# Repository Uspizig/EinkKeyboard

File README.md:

# EinkKeyboard

Please see full details here:
https://hackaday.io/project/185789-lowpow-e-ink-shortkeyboard-ble-wired-lorawifi

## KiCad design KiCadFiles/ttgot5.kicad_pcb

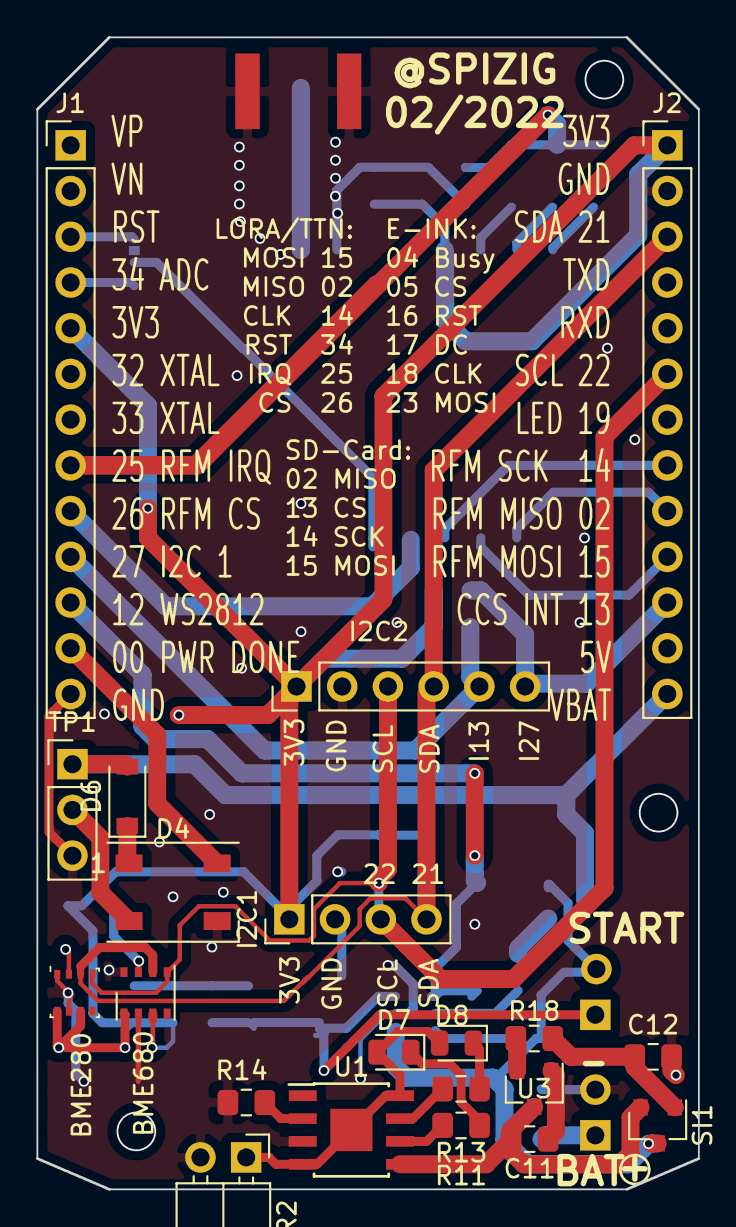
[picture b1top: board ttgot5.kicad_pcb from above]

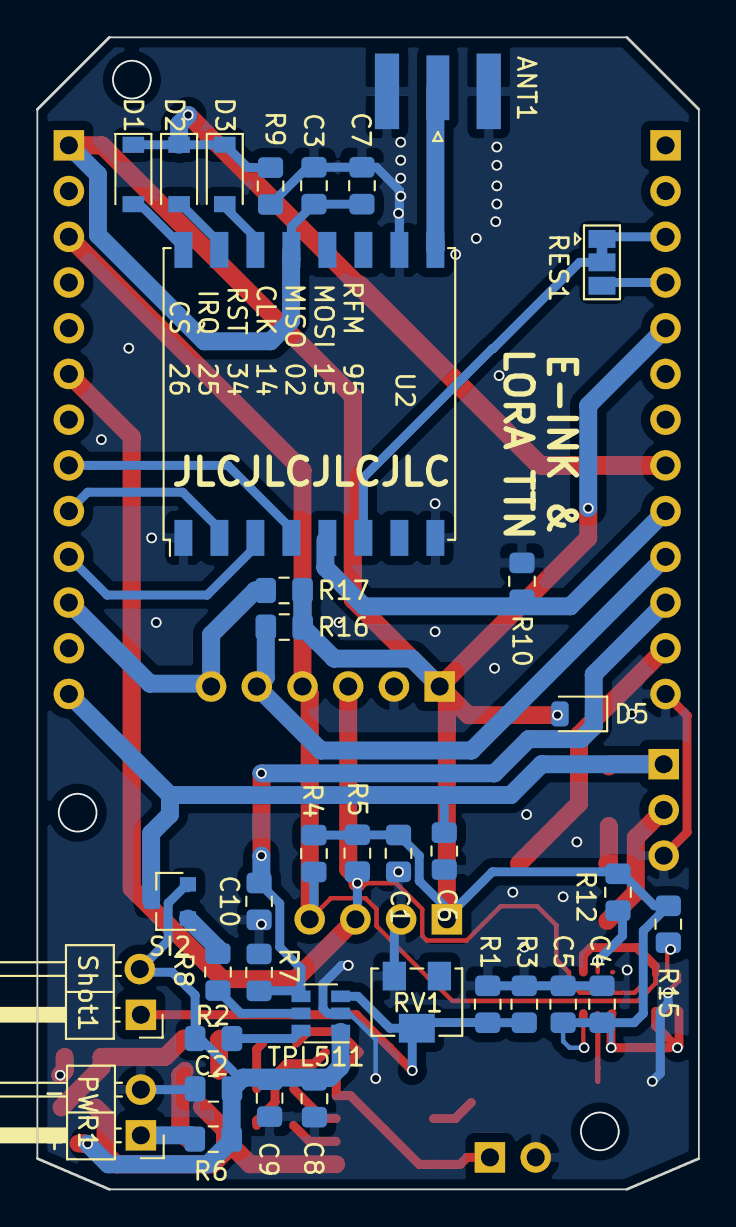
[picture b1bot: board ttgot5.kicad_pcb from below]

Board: 2 copper layers, 36.8 x 64.0 mm, 57 parts (36 on the bottom side), 40 nets.

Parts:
ANT1: Antenna; SMA_Samtec_SMA-J-P-H-ST-EM1_EdgeMount
BME280: BME280; Bosch_LGA-8_2.5x2.5mm_P0.65mm_ClockwisePinNumbering
BME680: BME680; Bosch_LGA-8_3x3mm_P0.8mm_ClockwisePinNumbering
C1, C4, C5, C6, C7, C9, C10, C11, C12: 100nF; C_0805_2012Metric_Pad1.15x1.40mm_HandSolder
C2: 100uF; C_0805_2012Metric_Pad1.15x1.40mm_HandSolder
C3: C; C_0805_2012Metric_Pad1.15x1.40mm_HandSolder
C8: 1nF; C_0805_2012Metric_Pad1.15x1.40mm_HandSolder
D1, D2, D3, D6: D; D_SOD-123
D4: WS2812B; LED_WS2812B_PLCC4_5.0x5.0mm_P3.2mm
D5, D7, D8: LED; LED_0805_2012Metric
I2C1: I2C; PinHeader_1x04_P2.54mm_Vertical
I2C2: I2C; PinHeader_1x06_P2.54mm_Vertical
J1: Con_L; PinHeader_1x13_P2.54mm_Vertical
J2: Con_R; PinHeader_1x13_P2.54mm_Vertical
PWR1, PWR2: PWR; PinHeader_1x02_P2.54mm_Horizontal
R1, R3: 340K; R_0805_2012Metric_Pad1.15x1.40mm_HandSolder
R2, R6, R12, R15: 0R; R_0805_2012Metric_Pad1.15x1.40mm_HandSolder
R4, R5, R16, R17: 4K7; R_0805_2012Metric_Pad1.15x1.40mm_HandSolder
R7: R; R_0805_2012Metric_Pad1.15x1.40mm_HandSolder
R8, R10: 100K; R_0805_2012Metric_Pad1.15x1.40mm_HandSolder
R9: 4.7k; R_0805_2012Metric_Pad1.15x1.40mm_HandSolder
R11, R13, R14, R18: 1K; R_0805_2012Metric_Pad1.15x1.40mm_HandSolder
RES1: RST; SolderJumper-3_P1.3mm_Bridged12_Pad1.0x1.5mm
RV1: R_POT; Potentiometer_Bourns_3224W_Vertical
SI1, SI2: SI2301CDS; SOT-23
Shot1: Shot; PinHeader_1x02_P2.54mm_Horizontal
TP1: TP; PinHeader_1x03_P2.54mm_Vertical
TPL511: TPL5110; SOT-23-6
U1: TP4056; tp4056
U2: RFM95W-915S2; HOPERF_RFM9XW_SMD
U3: AIC809-29 -GUTR; SOT-23

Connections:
+3V3: BME280.6, BME280.8, BME680.6, BME680.8, C1.2, C3.2, C4.1, C5.2, C7.2, D5.2, I2C1.1, I2C2.1, J1.5, J2.1, R4.1, R5.1, R12.2, R15.2, R16.1, R17.1, U2.13
+3V8: C11.2, SI1.2, U1.5, U3.3
+BATT: C6.2, D6.2, J2.13, SI2.3, TP1.1
/0: D4.4, J1.12
/2: J2.9, U2.2
/12: C10.2, D5.1, J1.11, R7.1, TPL511.4
/13: I2C2.6, J2.11, R17.2
/14: J2.8, U2.4
/15: J2.10, U2.3
/21_SDA: BME280.3, BME680.3, I2C1.4, I2C2.4, J2.3, R4.2
/22_SCL: BME280.4, BME680.4, I2C1.3, I2C2.3, J2.6, R5.2
/25: D1.1, D2.1, D3.1, J1.8, R9.1
/26: J1.9, R10.2, U2.5
/27: I2C2.5, J1.10, R16.2
/34: J1.4, RES1.3
/LORA_RESET: RES1.2, U2.6
/RST: J1.3, RES1.1
GND: ANT1.2, BME280.1, BME280.7, BME680.1, BME680.7, C1.1, C2.2, C3.1, C4.2, C5.1, C6.1, C7.1, C8.2, C9.2, C10.1, C11.1, C12.1, D4.3, I2C1.2, I2C2.2, J1.13, J2.2, PWR1.2, PWR2.2, R1.2, R3.2, R7.2, R9.2, R10.1, R14.2, RV1.3, TP1.3, TPL511.2, U1.3, U2.1, U2.8, U2.10, U3.1
unnamed: ANT1.1, U2.9
unnamed: BME280.2, R15.1
unnamed: BME680.2, R12.1
unnamed: C12.2, R18.1, SI1.1
unnamed: D1.2, U2.16
unnamed: D2.2, U2.15
unnamed: D3.2, U2.14
unnamed: D4.1, D6.1
unnamed: D4.2, TP1.2
unnamed: D7.1, R11.1
unnamed: D7.2, D8.2, PWR2.1, U1.4, U1.8
unnamed: D8.1, R13.1
unnamed: PWR1.1, R6.1
unnamed: R1.1, R3.1, RV1.2, Shot1.1, TPL511.3
unnamed: R2.2, TPL511.6
unnamed: R8.1, SI2.1
unnamed: R8.2, TPL511.5
unnamed: R11.2, U1.6
unnamed: R13.2, U1.7
unnamed: R14.1, U1.2
unnamed: R18.2, U3.2
VDC: C2.1, C8.1, C9.1, R2.1, R6.2, SI1.3, SI2.2, Shot1.2, TPL511.1
